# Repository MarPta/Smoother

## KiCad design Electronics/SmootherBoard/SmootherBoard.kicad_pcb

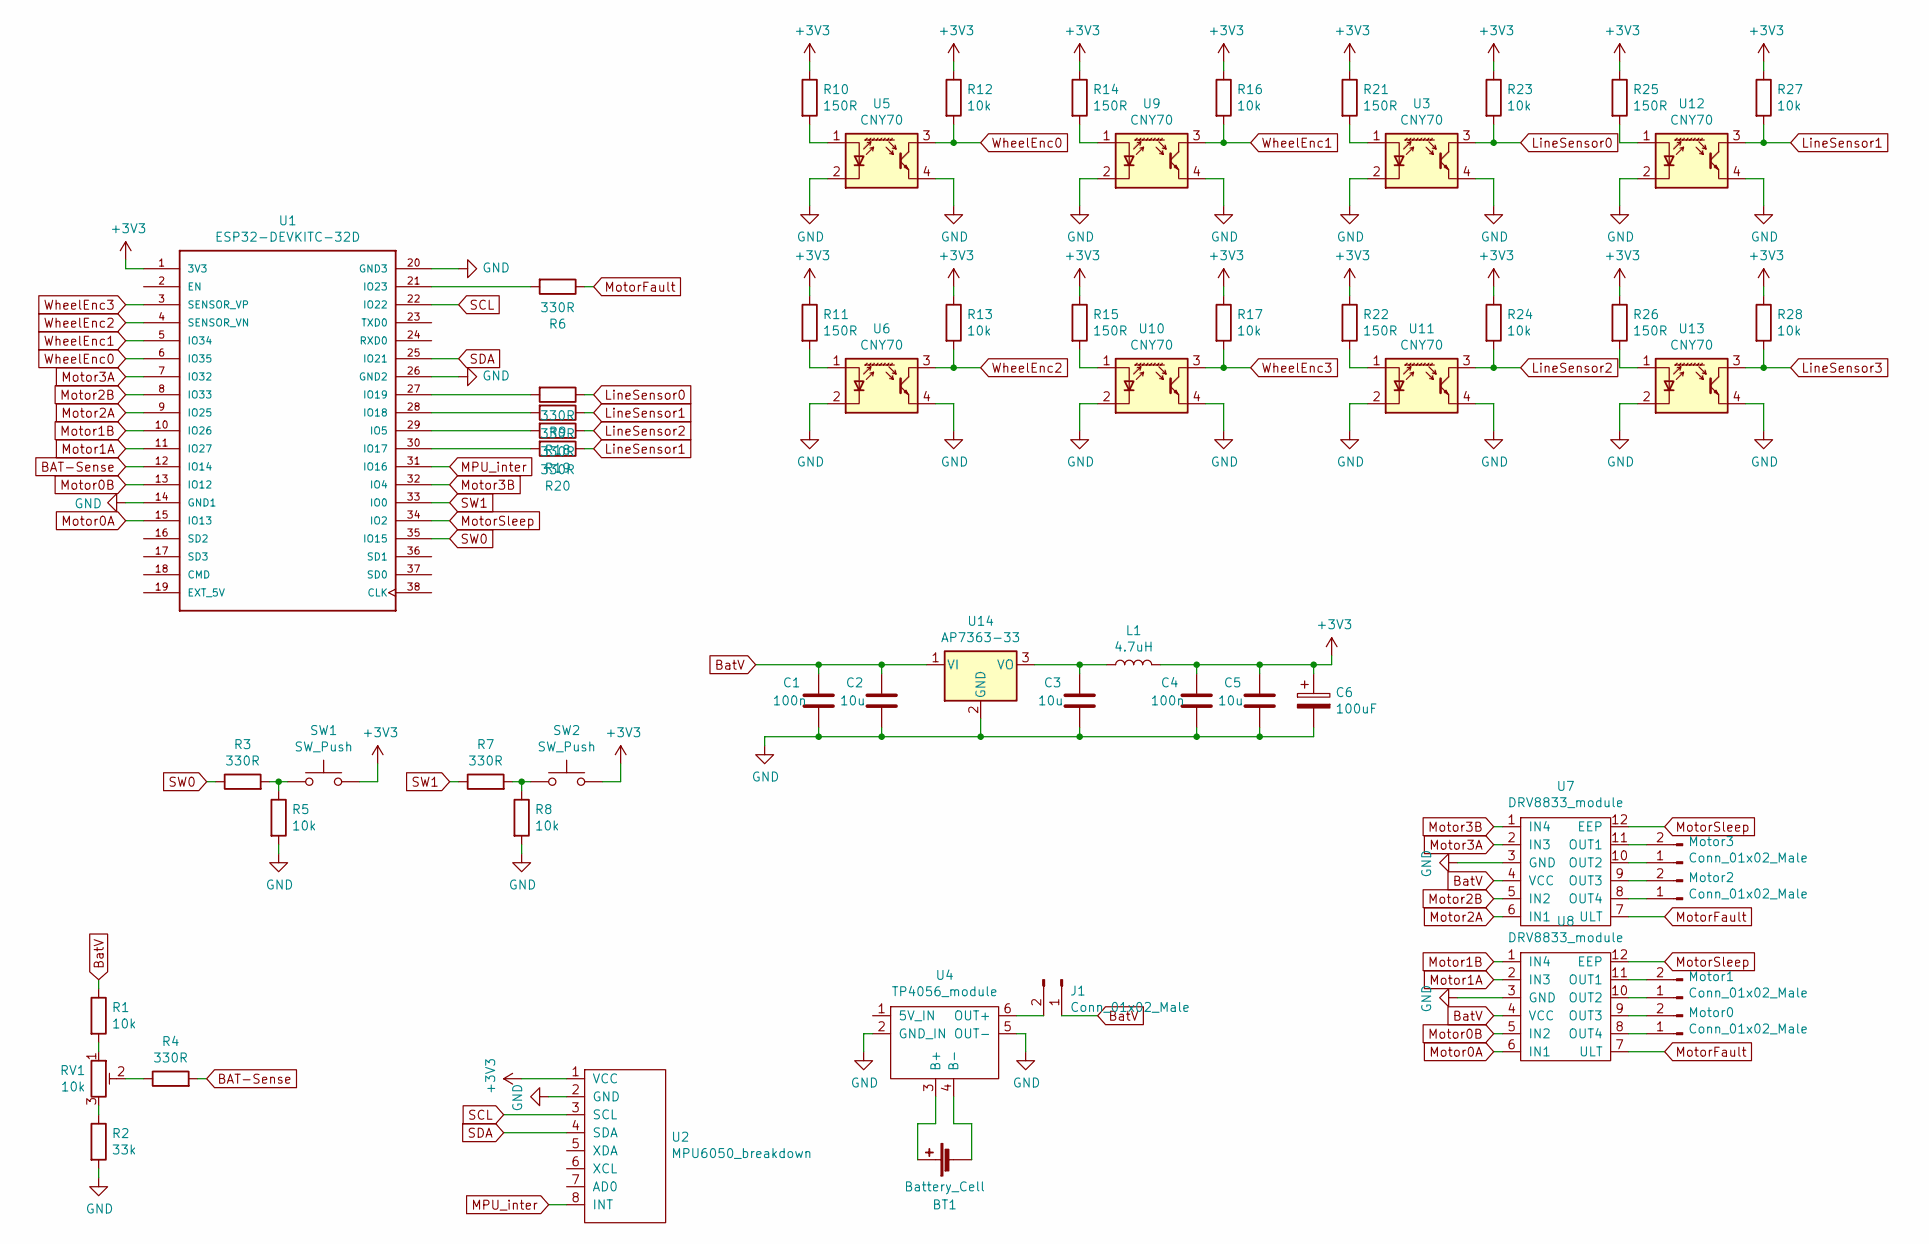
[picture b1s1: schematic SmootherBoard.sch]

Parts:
BT1: Battery_Cell; BatteryHolder_MPD_BH-18650-PC2
C1, C4: 100n; C_1206_3216Metric_Pad1.42x1.75mm_HandSolder
C2, C3, C5: 10u; C_1206_3216Metric_Pad1.42x1.75mm_HandSolder
C6: 100uF; CP_Radial_D8.0mm_P3.50mm
J1: Conn_01x02_Male; PinHeader_1x02_P2.54mm_Vertical
L1: 4.7uH; L_1206_3216Metric
Motor0, Motor1, Motor2, Motor3: Conn_01x02_Male; Motor
R1, R5, R8, R12, R13, R16, R17, R23, R24, R27, R28: 10k; R_1206_3216Metric_Pad1.42x1.75mm_HandSolder
R2: 33k; R_1206_3216Metric_Pad1.42x1.75mm_HandSolder
R3, R4, R6, R7, R9, R18, R19, R20: 330R; R_1206_3216Metric_Pad1.42x1.75mm_HandSolder
R10, R11, R14, R15, R21, R22, R25, R26: 150R; R_1206_3216Metric_Pad1.42x1.75mm_HandSolder
RV1: 10k; Potentiometer_Bourns_3296Y_Vertical
SW1, SW2: SW_Push; SW_PUSH_6mm
U1: ESP32-DEVKITC-32D; MODULE_ESP32-DEVKITC-32D
U2: MPU6050_breakdown; MPU6050_Breakdown
U3, U5, U6, U9, U10, U11, U12, U13: CNY70; Vishay_CNY70
U4: TP4056_module
U7, U8: DRV8833_module
U14: AP7363-33; TO-252-3_TabPin2

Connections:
+3V3: C4.1, C5.1, C6.1, L1.2, R10.1, R11.1, R12.1, R13.1, R14.1, R15.1, R16.1, R17.1, R21.1, R22.1, R23.1, R24.1, R25.1, R26.1, R27.1, R28.1, SW1.2, SW2.2, U1.1 (3V3), U2.1 (VCC)
BAT-Sense: R4.2, U1.12 (IO14)
BatV: C1.1, C2.1, J1.1, R1.1, U7.4 (VCC), U8.4 (VCC), U14.1 (VI)
GND: C1.2, C2.2, C3.2, C4.2, C5.2, C6.2, R2.2, R5.2, R8.2, U1.14 (GND1), U1.20 (GND3), U1.26 (GND2), U2.2 (GND), U3.2 (K), U3.4 (E), U4.2 (GND_IN), U4.5 (OUT-), U5.2 (K), U5.4 (E), U6.2 (K), U6.4 (E), U7.3 (GND), U8.3 (GND), U9.2 (K), U9.4 (E), U10.2 (K), U10.4 (E), U11.2 (K), U11.4 (E), U12.2 (K), U12.4 (E), U13.2 (K), U13.4 (E), U14.2 (GND)
LineSensor0: R9.1, R23.2, U3.3 (C)
LineSensor1: R18.1, R20.1, R27.2, U12.3 (C)
LineSensor2: R19.1, R24.2, U11.3 (C)
LineSensor3: R28.2, U13.3 (C)
MPU_inter: U1.31 (IO16), U2.8 (INT)
Motor0A: U1.15 (IO13), U8.6 (IN1)
Motor0B: U1.13 (IO12), U8.5 (IN2)
Motor1A: U1.11 (IO27), U8.2 (IN3)
Motor1B: U1.10 (IO26), U8.1 (IN4)
Motor2A: U1.9 (IO25), U7.6 (IN1)
Motor2B: U1.8 (IO33), U7.5 (IN2)
Motor3A: U1.7 (IO32), U7.2 (IN3)
Motor3B: U1.32 (IO4), U7.1 (IN4)
MotorFault: R6.1, U7.7 (ULT), U8.7 (ULT)
MotorSleep: U1.34 (IO2), U7.12 (EEP), U8.12 (EEP)
unnamed: BT1.1 (+), U4.3 (B+)
unnamed: BT1.2 (-), U4.4 (B-)
unnamed: C3.1, L1.1, U14.3 (VO)
unnamed: J1.2, U4.6 (OUT+)
unnamed: Motor0.1, U8.8 (OUT4)
unnamed: Motor0.2, U8.9 (OUT3)
unnamed: Motor1.1, U8.10 (OUT2)
unnamed: Motor1.2, U8.11 (OUT1)
unnamed: Motor2.1, U7.8 (OUT4)
unnamed: Motor2.2, U7.9 (OUT3)
unnamed: Motor3.1, U7.10 (OUT2)
unnamed: Motor3.2, U7.11 (OUT1)
unnamed: R1.2, RV1.1
unnamed: R2.1, RV1.3
unnamed: R3.2, R5.1, SW1.1
unnamed: R4.1, RV1.2
unnamed: R6.2, U1.21 (IO23)
unnamed: R7.2, R8.1, SW2.1
unnamed: R9.2, U1.27 (IO19)
unnamed: R10.2, U5.1 (A)
unnamed: R11.2, U6.1 (A)
unnamed: R14.2, U9.1 (A)
unnamed: R15.2, U10.1 (A)
unnamed: R18.2, U1.28 (IO18)
unnamed: R19.2, U1.29 (IO5)
unnamed: R20.2, U1.30 (IO17)
unnamed: R21.2, U3.1 (A)
unnamed: R22.2, U11.1 (A)
unnamed: R25.2, U12.1 (A)
unnamed: R26.2, U13.1 (A)
SCL: U1.22 (IO22), U2.3 (SCL)
SDA: U1.25 (IO21), U2.4 (SDA)
SW0: R3.1, U1.35 (IO15)
SW1: R7.1, U1.33 (IO0)
WheelEnc0: R12.2, U1.6 (IO35), U5.3 (C)
WheelEnc1: R16.2, U1.5 (IO34), U9.3 (C)
WheelEnc2: R13.2, U1.4 (SENSOR_VN), U6.3 (C)
WheelEnc3: R17.2, U1.3 (SENSOR_VP), U10.3 (C)

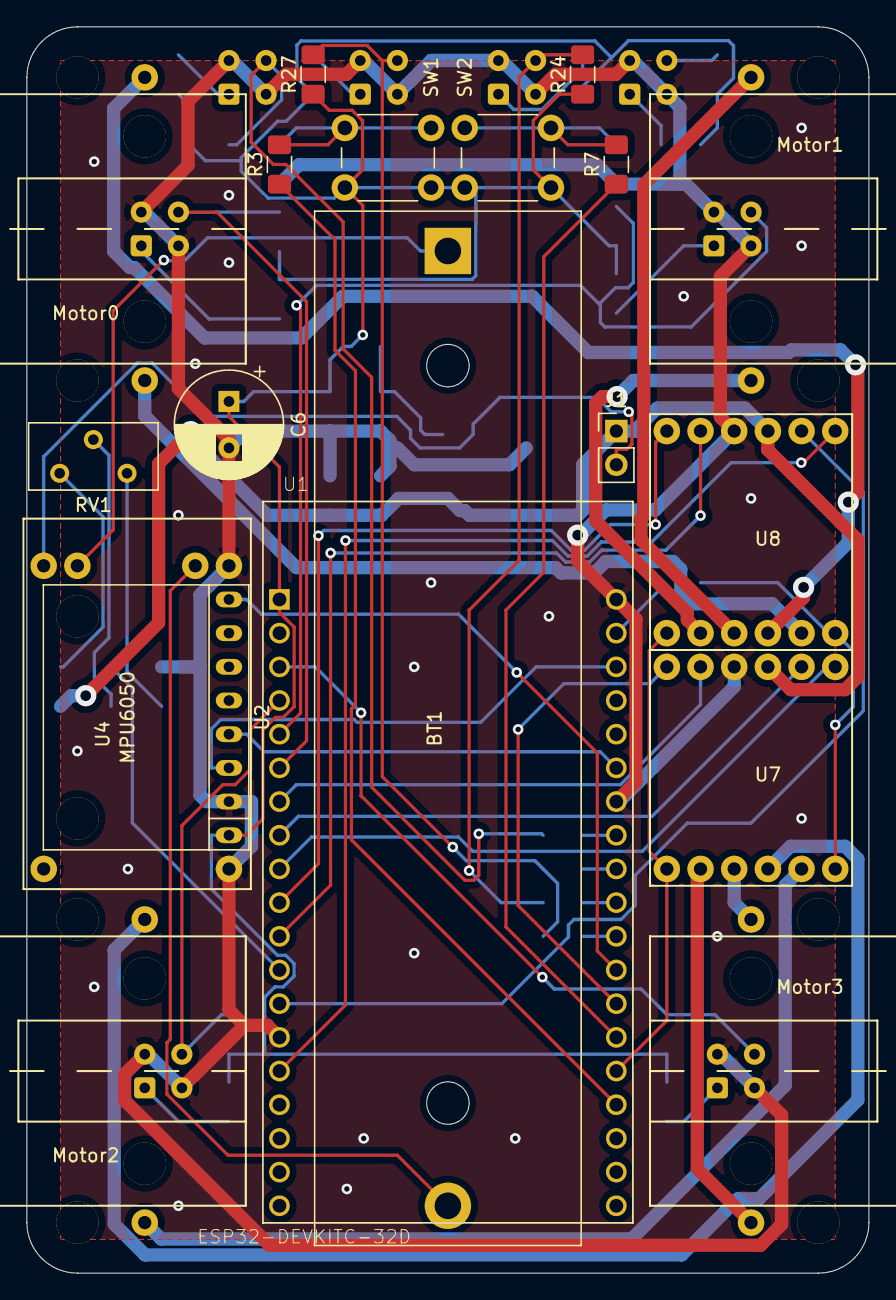
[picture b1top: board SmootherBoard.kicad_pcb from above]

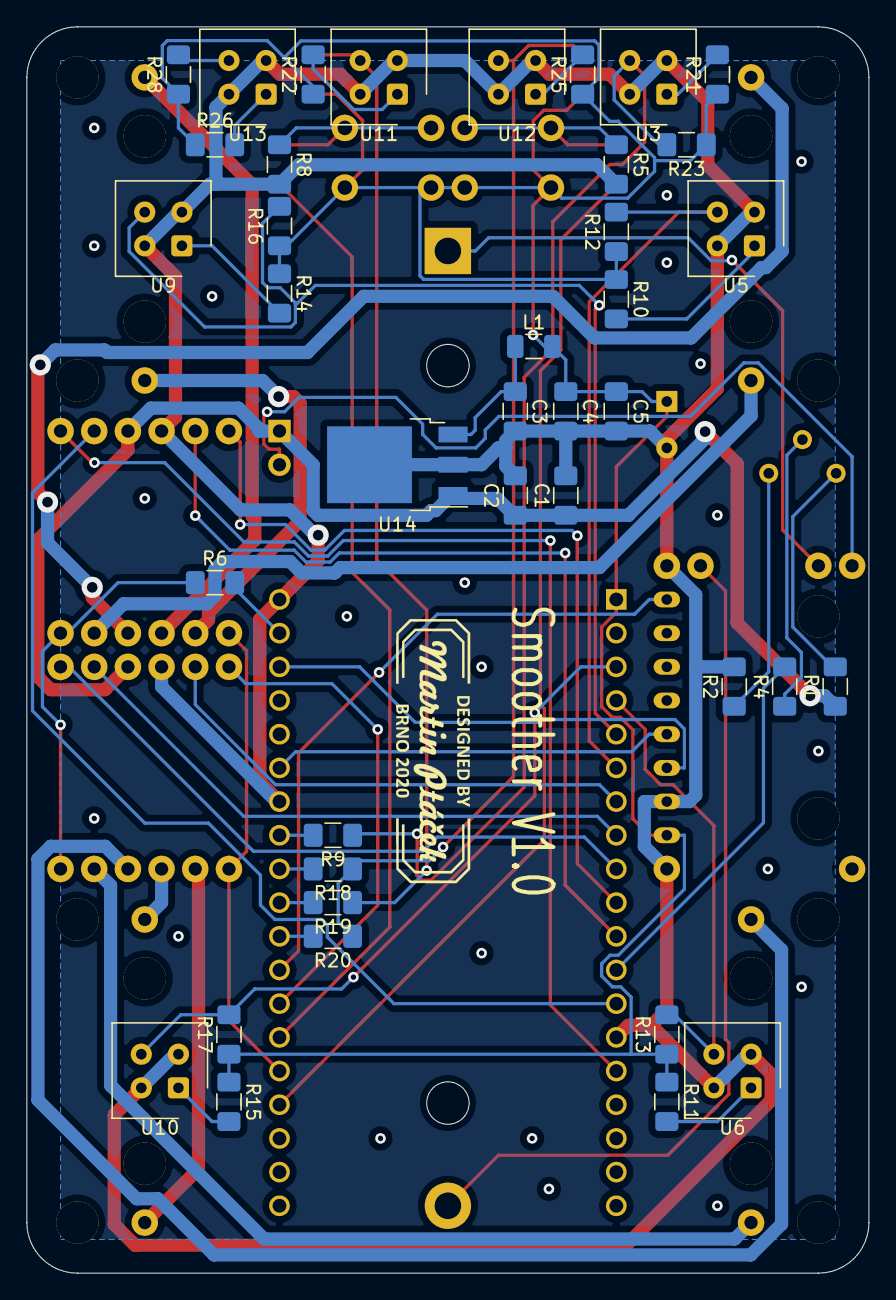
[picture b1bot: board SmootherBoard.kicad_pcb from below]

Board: 2 copper layers, 63.5 x 94.0 mm, 58 parts (39 on the bottom side), 57 nets.

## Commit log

2020-03-17 First schematic & footprints.
2020-03-17 Changed for ESP32. Added signature, 3V3 LDR.
2020-03-17 Board first completed.
2020-03-17 Generated manufacturing files.
2020-03-20 Changed LDO package for sot-252.
